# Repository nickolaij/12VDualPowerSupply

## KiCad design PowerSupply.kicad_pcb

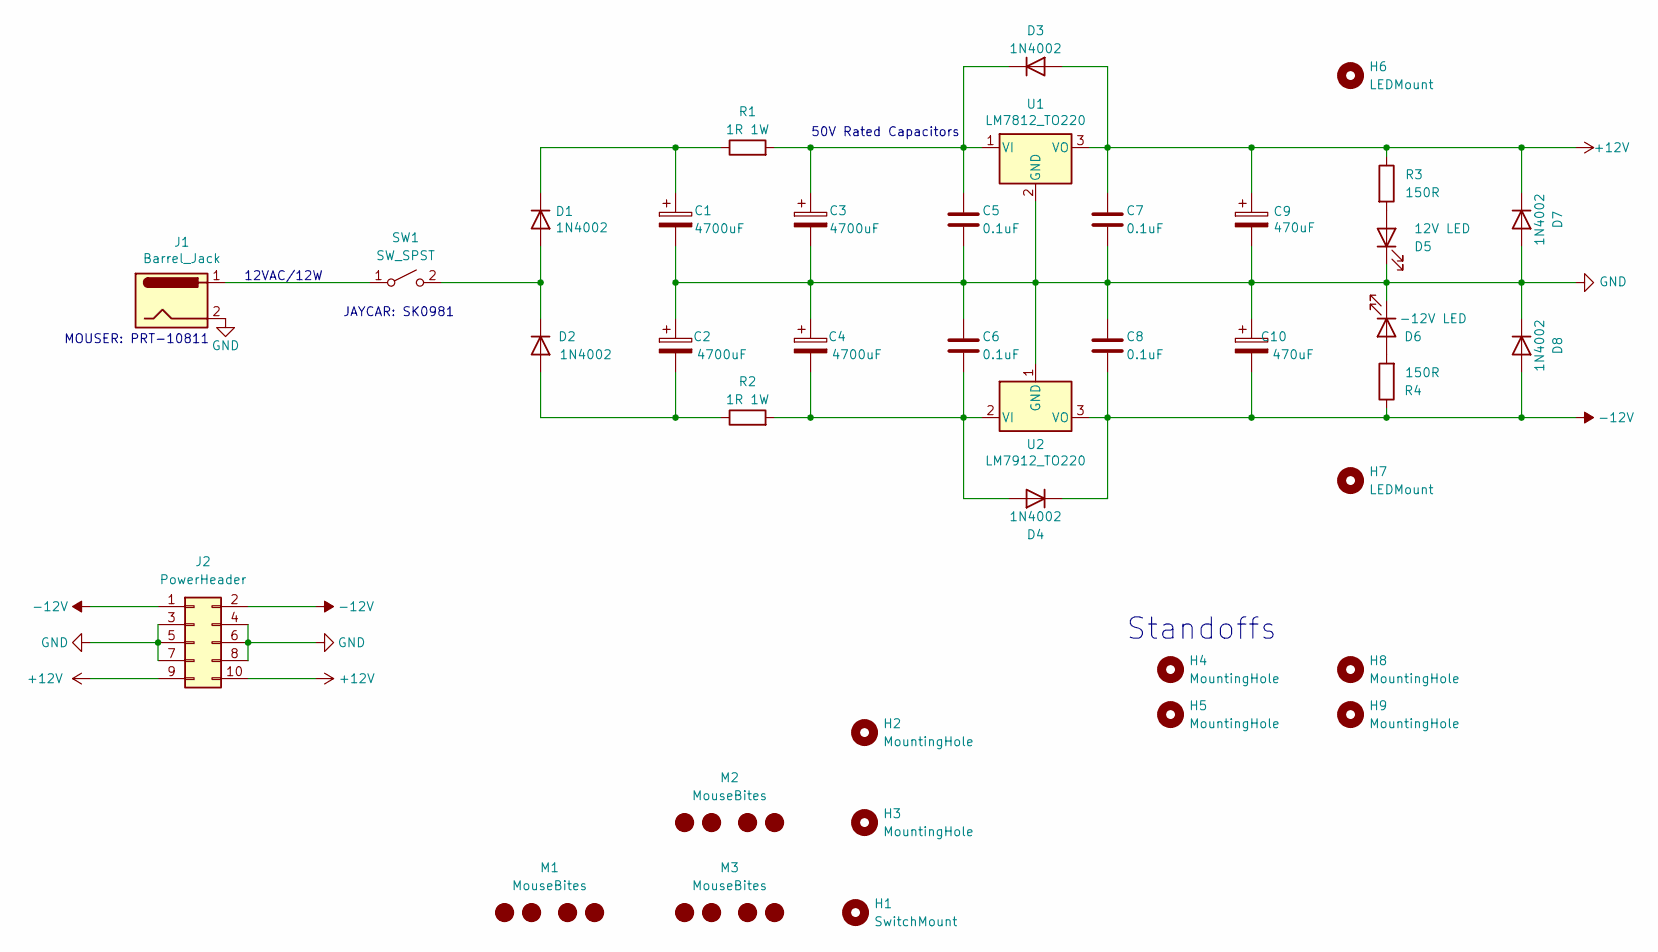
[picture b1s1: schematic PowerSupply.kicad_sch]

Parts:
C1, C2, C3, C4: 4700uF; CP_Radial_D22.0mm_P10.00mm_SnapIn
C5, C6, C7, C8: 0.1uF; C_0805_2012Metric_Pad1.18x1.45mm
C9, C10: 470uF; CP_Radial_D10.0mm_P5.00mm
D1, D2, D3, D4, D7, D8: 1N4002; D_T-1_P5.08mm_Horizontal
D5: 12V LED; LED_D5.0mm
D6: -12V LED; LED_D5.0mm
H1: SwitchMount
H2, H3: MountingHole; MountingHole_5.3mm_M5
H4, H5, H8, H9: MountingHole; MountingHole_3.2mm_M3
H6, H7: LEDMount; MountingHole_5mm
J1: Barrel_Jack; BarrelJack
J2: PowerHeader; IDC-Header_2x05_P2.54mm_Vertical
M1, M2, M3: MouseBites; mouse-bite-5mm-slot
R1, R2: 1R 1W; R_Axial_DIN0414_L11.9mm_D4.5mm_P15.24mm_Horizontal
R3, R4: 150R; R_0805_2012Metric_Pad1.20x1.40mm
SW1: SW_SPST; SolderWire-1.5sqmm_1x02_P6mm_D1.7mm_OD3mm
U1: LM7812_TO220; TO-220-3_Vertical
U2: LM7912_TO220; TO-220-3_Vertical

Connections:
+12V: C7.1, C9.1, D3.2 (A), D7.1 (K), J2.9, J2.10, R3.1, U1.3 (VO)
-12V: C8.2, C10.2, D4.1 (K), D8.2 (A), J2.1, J2.2, R4.1, U2.3 (VO)
GND: C1.2, C2.1, C3.2, C4.1, C5.2, C6.1, C7.2, C8.1, C9.2, C10.1, D5.1 (K), D6.1 (K), D7.2 (A), D8.1 (K), J1.2, J2.3, J2.4, J2.5, J2.6, J2.7, J2.8, U1.2 (GND), U2.1 (GND)
unnamed: C1.1, D1.1 (K), R1.1
unnamed: C2.2, D2.2 (A), R2.1
unnamed: C3.1, C5.1, D3.1 (K), R1.2, U1.1 (VI)
unnamed: C4.2, C6.2, D4.2 (A), R2.2, U2.2 (VI)
unnamed: D1.2 (A), D2.1 (K), SW1.2 (B)
unnamed: D5.2 (A), R3.2
unnamed: D6.2 (A), R4.2
unnamed: J1.1, SW1.1 (A)

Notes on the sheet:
JAYCAR: SK0981
MOUSER: PRT-10811
50V Rated Capacitors
12VAC/12W
Standoffs

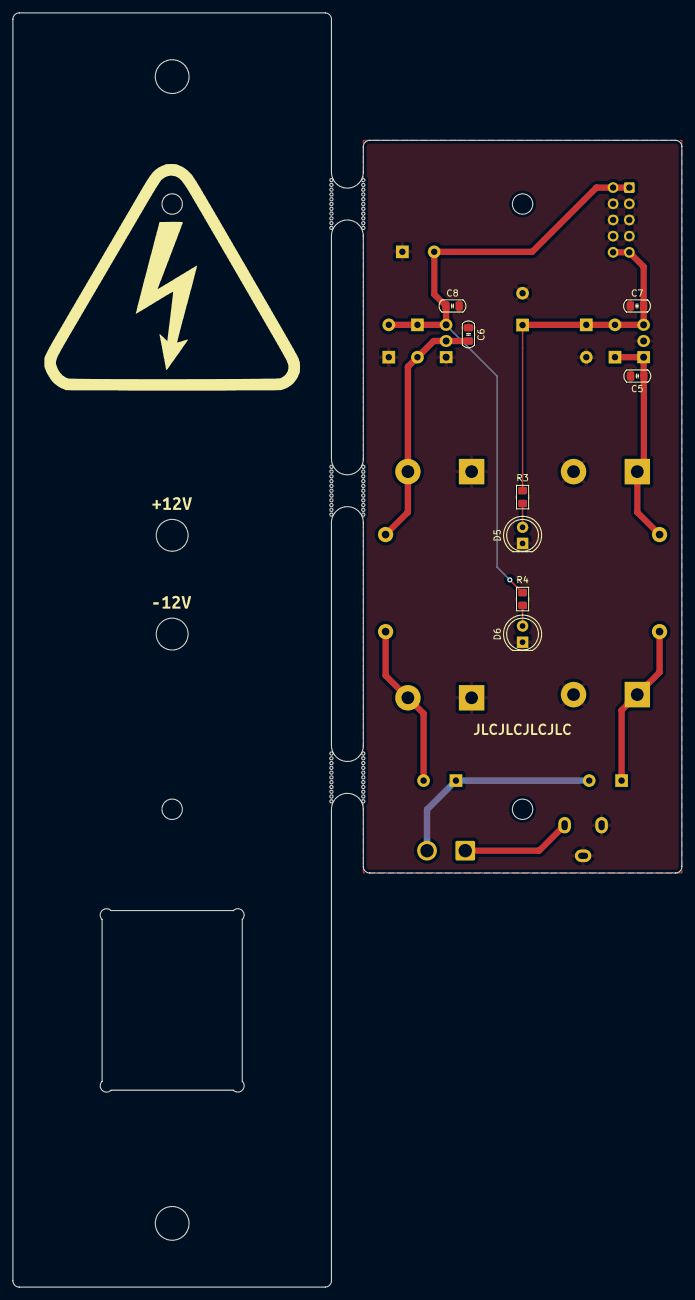
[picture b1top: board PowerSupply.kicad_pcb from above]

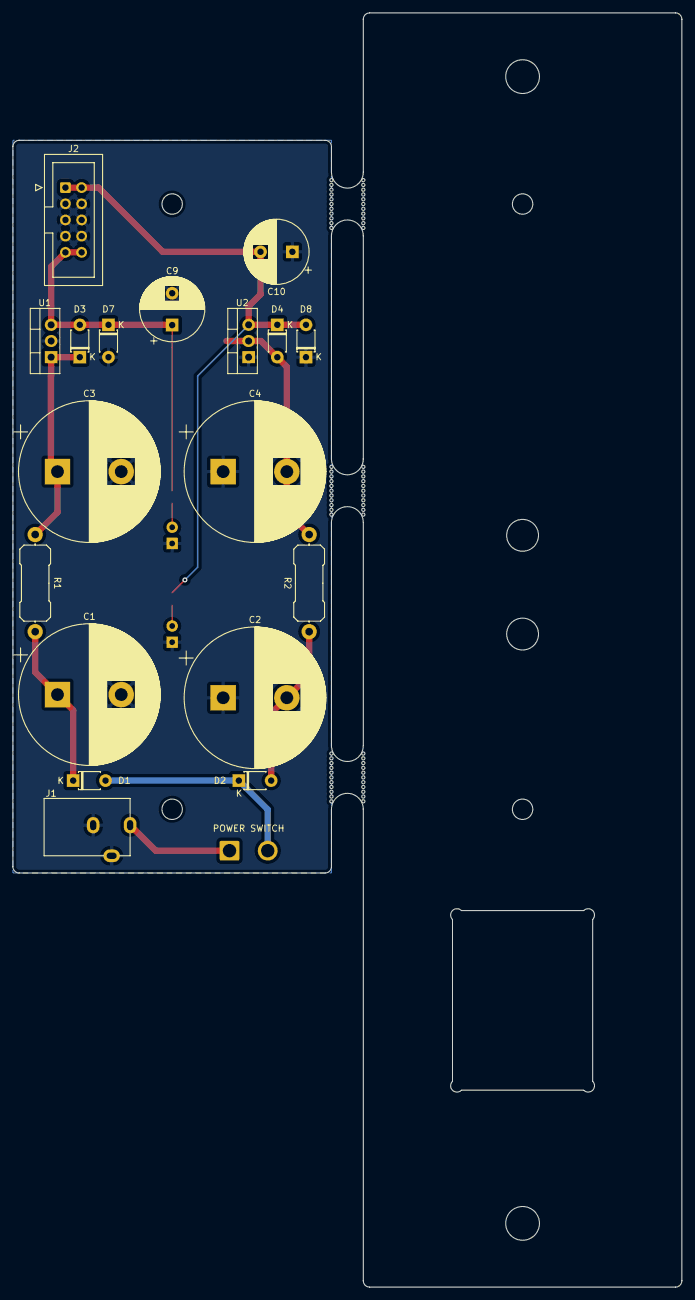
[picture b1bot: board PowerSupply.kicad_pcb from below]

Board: 2 copper layers, 105.0 x 200.0 mm, 41 parts (18 on the bottom side), 11 nets.

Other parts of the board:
kibuzzard-61F37152: G***; kibuzzard-61F37152
kibuzzard-61F37174: G***; kibuzzard-61F37174

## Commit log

2022-01-20 Schematic almost complete
2022-01-24 more uFs
2022-01-26 layout started
2022-01-28 Gerbers sent for production
2022-01-28 Add Moutning Holes
2022-01-28 Panelisation and knob placement finished
2022-01-31 Changed IDC to 2x5
2022-04-12 Preliminary design on rework
2022-07-14 Production v2
